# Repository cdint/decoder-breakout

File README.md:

# decoder-breakout
High-speed optical decoder breakout board with an I2C interface

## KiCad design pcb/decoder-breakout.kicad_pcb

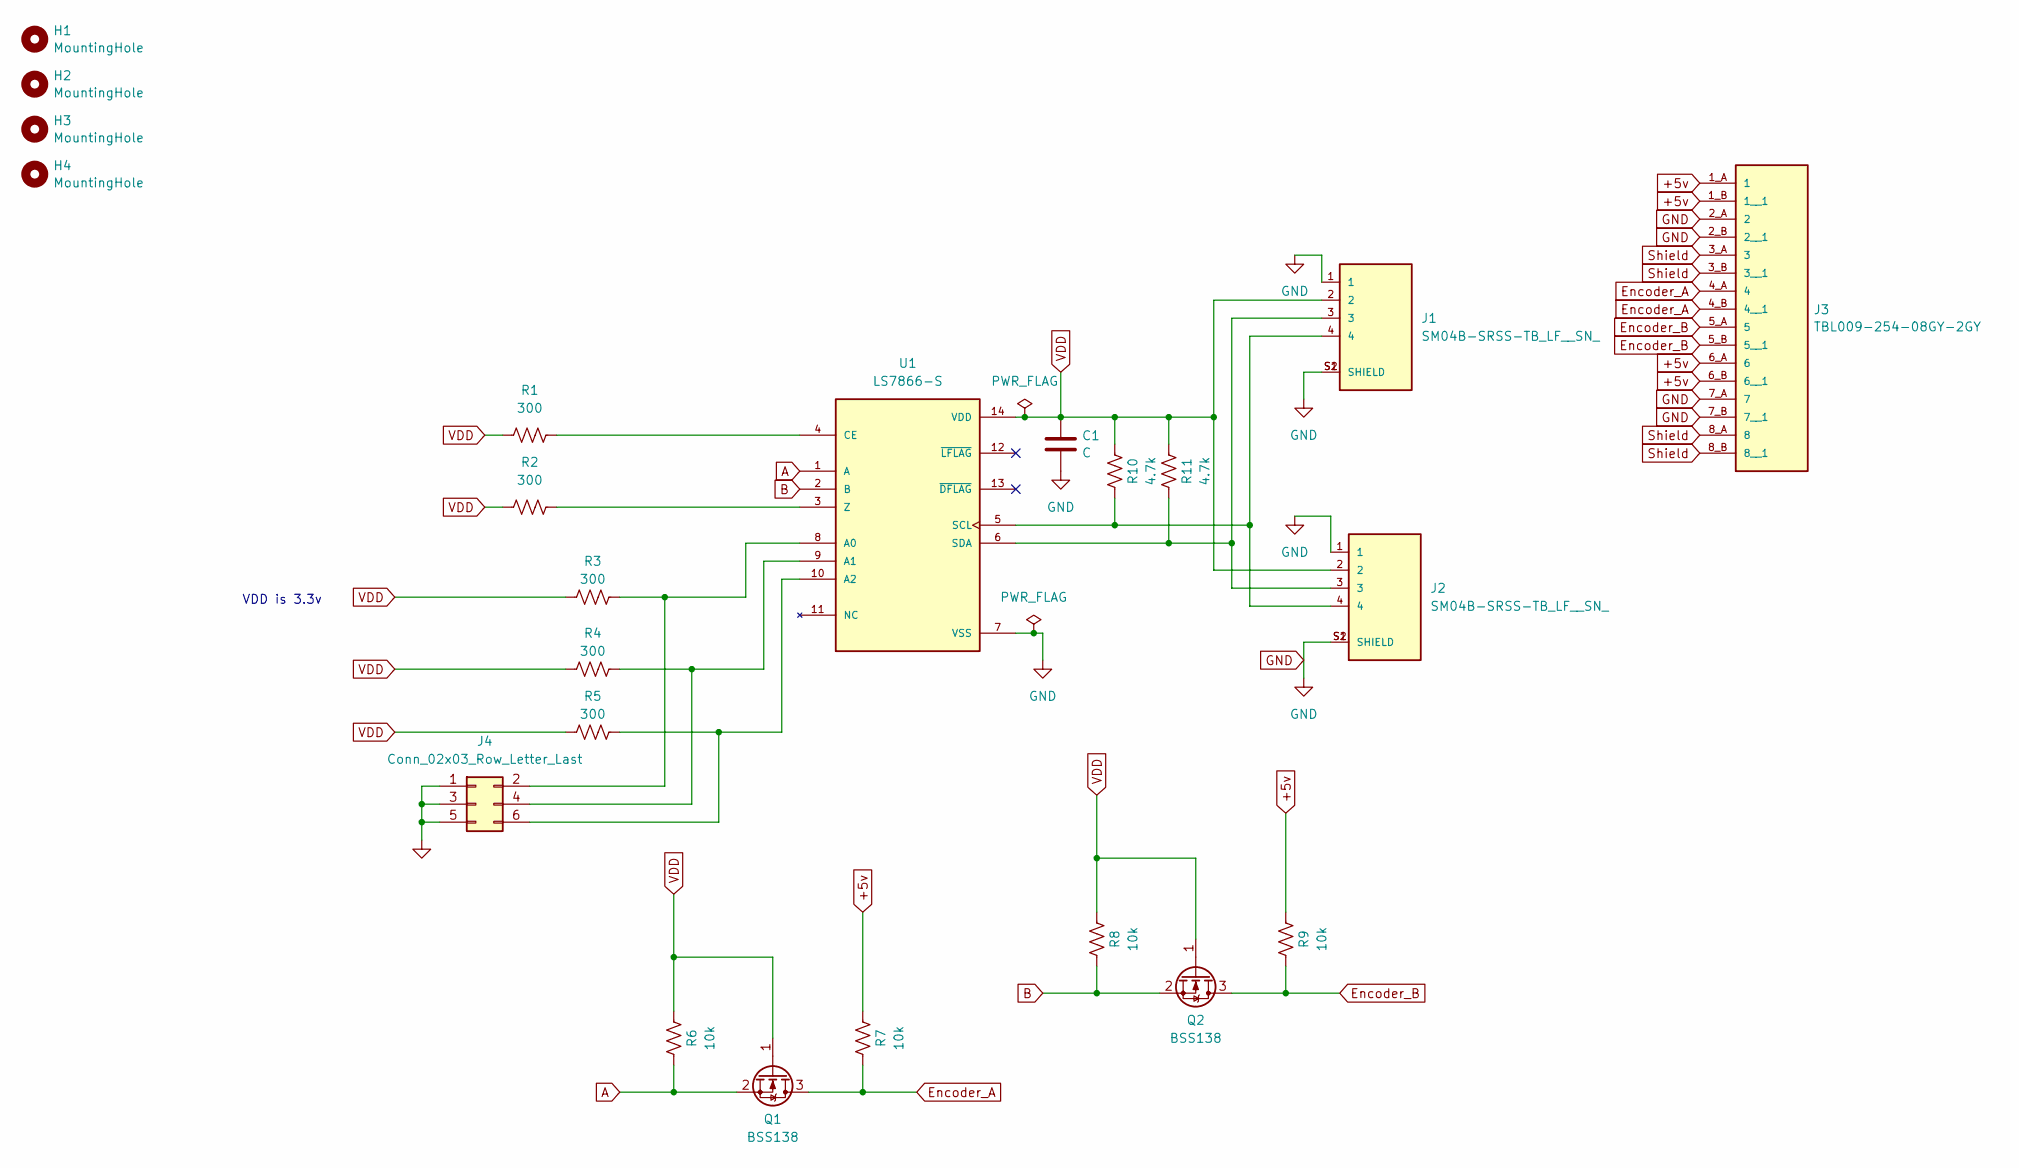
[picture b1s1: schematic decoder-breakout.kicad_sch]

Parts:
C1: C; C_1812_4532Metric_Pad1.57x3.40mm_HandSolder
H1, H2, H3, H4: MountingHole; MountingHole_2.5mm_Pad
J1, J2: SM04B-SRSS-TB_LF__SN_; JST_SM04B-SRSS-TB_LF__SN_
J3: TBL009-254-08GY-2GY; CUI_TBL009-254-08GY-2GY
J4: Conn_02x03_Row_Letter_Last; PinHeader_2x03_P2.54mm_Vertical
Q1, Q2: BSS138; SOT-23
R1, R2, R3, R4, R5: 300; R_2010_5025Metric_Pad1.40x2.65mm_HandSolder
R6, R7, R8, R9: 10k; R_2010_5025Metric_Pad1.40x2.65mm_HandSolder
R10, R11: 4.7k; R_2010_5025Metric_Pad1.40x2.65mm_HandSolder
U1: LS7866-S; SOIC127P600X175-14N; PARTREV June 2023

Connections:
+5v: J3.1_A (1), J3.1_B (1__1), J3.6_A (6), J3.6_B (6__1), R7.1, R9.1
A: Q1.2 (S), R6.2, U1.1 (A)
B: Q2.2 (S), R8.2, U1.2 (B)
Encoder_A: J3.4_A (4), J3.4_B (4__1), Q1.3 (D), R7.2
Encoder_B: J3.5_A (5), J3.5_B (5__1), Q2.3 (D), R9.2
GND: C1.2, J1.1, J1.S1 (SHIELD), J1.S2 (SHIELD), J2.1, J2.S1 (SHIELD), J2.S2 (SHIELD), J3.2_A (2), J3.2_B (2__1), J3.7_A (7), J3.7_B (7__1), J4.1, J4.3, J4.5, U1.7 (VSS)
unnamed: J4.2, R3.1, U1.8 (A0)
unnamed: J4.6, R5.1, U1.10 (A2)
unnamed: J4.4, R4.1, U1.9 (A1)
unnamed: R1.1, U1.4 (CE)
unnamed: J1.4, J2.4, R10.2, U1.5 (SCL)
unnamed: J1.3, J2.3, R11.2, U1.6 (SDA)
unnamed: R2.1, U1.3 (Z)
Shield: J3.3_A (3), J3.3_B (3__1), J3.8_A (8), J3.8_B (8__1)
VDD: C1.1, J1.2, J2.2, Q1.1 (G), Q2.1 (G), R1.2, R2.2, R3.2, R4.2, R5.2, R6.1, R8.1, R10.1, R11.1, U1.14 (VDD)

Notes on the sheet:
VDD is 3.3v

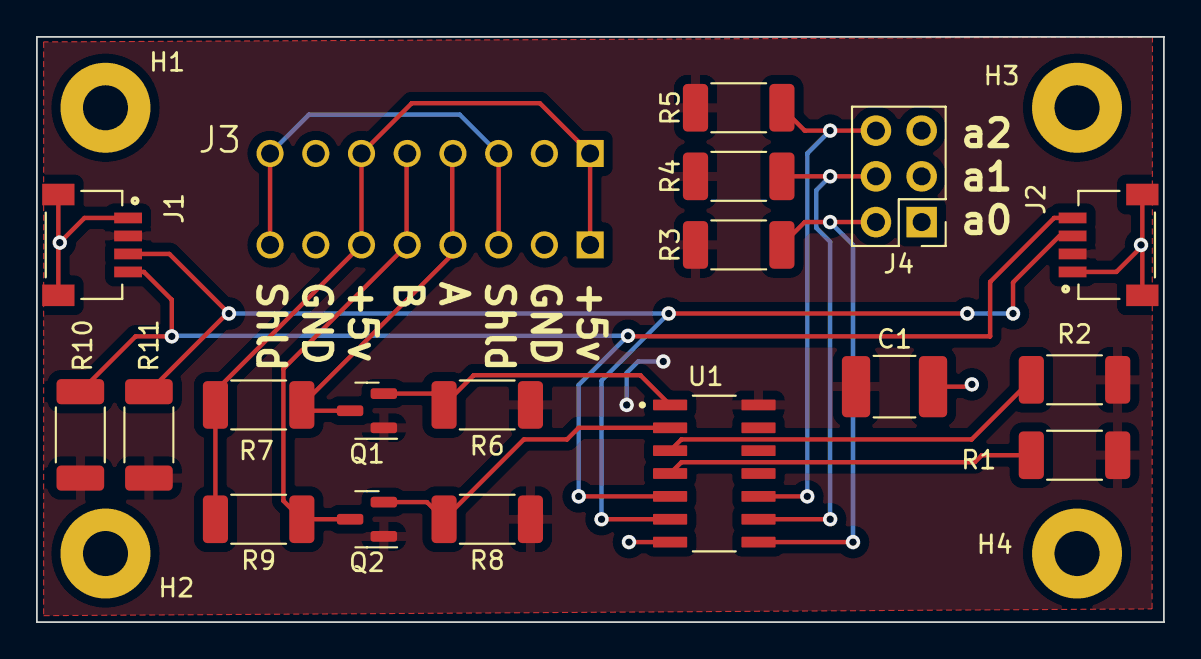
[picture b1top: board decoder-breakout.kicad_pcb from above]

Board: 2 copper layers, 62.6 x 32.5 mm, 23 parts (0 on the bottom side), 15 nets.

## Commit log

2024-04-16 initial commit, add LS7866 symbol and footprint
2024-05-09 add resistors and jumpers
2024-05-30 added jumpers for changing address, level shifters 3.3v->5v for encoders
2024-05-30 added terminal block, started on PCB
2024-07-02 pcb rough layout
2024-07-02 pcb adding filled zones and starting connections
2024-07-09 corrected jumper wiring
2024-07-09 clean up terminal block pins
    - add 10 and 14 pin terminal blocks for possible use in the future
2024-07-16 working on copper fill
2024-07-16 add decoupling cap, mounting holes and board edges
2024-08-06 Split terminal, add PCB screen print, consider shield-ground jumper
    Split terminal, add PCB screen print, consider shield-ground jumper
    summary of diff --git a/TODO.md b/TODO.md
    - Split terminal block into two: one for 5 pins for encoder, another for +5v, gnd, and shield
    - Add screen print to the PCB for identifying connections, possibly with a graphic for encoder connections
    - Consider adding a jumper to optionally connect shield and ground together
2024-08-06 WIP set up particle workbench and get compile working
2024-08-27 Replace HAL_I2C with Wire.write, update LS7866 headers
    Replace HAL_I2C_Mem_Write with Wire.write() in write_reg
    summary of diff --git a/src/photon2/src/LS7866.cpp b/src/photon2/src/LS7866.cpp
    - Add a comment to replace HAL_I2C_Mem_Write with Wire.write() in write_reg method
    Add stdint.h header, comment out i2c_hal in LS7866 class
    summary of diff --git a/src/photon2/src/LS7866.h b/src/photon2/src/LS7866.h
    - Include `<stdint.h>` header
2024-09-10 WIP LS7866 and photon 2 demo code
    - temporarily move src/* to .../junk/
    - experiment with demo code from https://lsicsi.com/products/ls7866/
2024-09-10 Disable counter 0, LED, SyncPin; enable counter 7; adjust I2C
    Disable counter 0, LED, SyncPin; enable counter 7; adjust I2C.
    summary of diff --git a/src/photon2/src/decoder-breakout.cpp b/src/photon2/src/decoder-breakout.cpp
    - Remove usage of counter 0 by commenting out its definition
    - Define counter 7 for use
    - Comment out LED and SyncPin related lines, effectively disabling LED operations and the usage of SyncPin
    - Disable `setLed` function calls by commenting them out in various parts of the code
2024-09-19 Update version, simplify chip setup, remove LED code
    Update PRM_VERSION, simplify chip setup, remove LED code
    summary of diff --git a/src/photon2/src/decoder-breakout.cpp b/src/photon2/src/decoder-breakout.cpp
    - Change PRM_VERSION from "1.00" to "0.1"
    - Comment out the definition of CNTR_7
    - Introduce definitions for ADDR_JUMPERS and CHIP_ADDR
    - Remove definitions for LED related constants and operations
2024-09-19 Add newline to Serial.print in ChipSetup and setup function
    Add newline to Serial.print and version message in setup
    summary of diff --git a/src/photon2/src/decoder-breakout.cpp b/src/photon2/src/decoder-breakout.cpp
    - Add newline character to Serial.print message in ChipSetup
    - Append newline character to version display message in setup function
2024-09-26 added I2C scanner
2024-10-03 Clarify LS7866 address bits; rename variable and update references.
    Clarify LS7866 high-order address bits fixed at 0x70
    summary of diff --git a/src/photon2/src/LS7866_Registers.h b/src/photon2/src/LS7866_Registers.h
    - Add comment to clarify that LS7866 high-order address bits are fixed at 0x70
    Rename variable and update its references in functions
    summary of diff --git a/src/photon2/src/decoder-breakout.cpp b/src/photon2/src/decoder-breakout.cpp
    - Rename `tsPollingInterval` variable to `nextPollMillis` in decoder-breakout.cpp
2024-10-03 Set firmware 5.8.0, p2; update I2C, fix includes, continuous scan.
    Add particle firmwareVersion 5.8.0 and targetPlatform p2
    summary of diff --git a/src/photon2addressScanner/.vscode/settings.json b/src/photon2addressScanner/.vscode/settings.json
    - Add "particle.firmwareVersion" with a value of "5.8.0"
    - Add "particle.targetPlatform" with a value of "p2"
    Update I2C scanner code for continuous scanning, fix includes
    summary of diff --git a/src/photon2addressScanner/src/L07_00_I2CScanner.cpp b/src/photon2addressScanner/src/L07_00_I2CScanner.cpp
2024-10-03 changed lowercase to Wire.h, set OS version
2024-10-17 Adjust PCB design, skip I2C reserved addresses, tweak delays
    Move, add junctions; adjust wires; update symbols, labels
    summary of diff --git a/pcb/decoder-breakout.kicad_sch b/pcb/decoder-breakout.kicad_sch
    - Move some junctions to new coordinates on the schematic
    - Add new junctions with unique UUIDs
    - Adjust wire connections to match new junction positions
    - Remove a junction and its associated wires
2024-10-24 Update CounterPoll format, disable Fast Mode, reduce delay
    Update CounterPoll format, disable Fast Mode, reduce delay
    summary of diff --git a/src/photon2/src/decoder-breakout.cpp b/src/photon2/src/decoder-breakout.cpp
    - Update formatting in CounterPoll function to include both decimal and hex representations of the counter value in the printed message
    - Disable setting I2C bus speed to Fast Mode 400K in setup function
    - Reduce the initial delay in setup function from 10000ms to 5000ms to accelerate startup
2024-11-07 Add BSS138_1 symbol, update datasheet position, change lib_id.
    Add BSS138_1 symbol; update datasheet position and lib_id
    summary of diff --git a/pcb/decoder-breakout.kicad_sch b/pcb/decoder-breakout.kicad_sch
    - Add symbol for BSS138_1 with properties including Reference, Value, Footprint, Datasheet, ki_keywords, ki_description, and ki_fp_filters
    - Define graphical representation with polylines and circles for BSS138_1 symbol, including stroke and fill specifications
    - Define pins for BSS138_1 symbol with names G, S, D and their respective positions and numbers
    - Update the Datasheet property position for existing elements to (5.08 -3.81 0)
2024-11-07 v0.1 as built
    Update components, adjust layers, change directory, add elements
    summary of diff --git a/pcb/decoder-breakout.kicad_pcb b/pcb/decoder-breakout.kicad_pcb
    - Update references and values for components Q2 and Q1
    - Adjust various line strokes and polygon fills on F.SilkS and F.CrtYd layers
    - Change model directory reference from KICAD6_3DMODEL_DIR to KICAD7_3DMODEL_DIR
    - Add new resistor footprints with specified attributes and dimensions
2024-11-07 generate BOM for v0.1
    Comment out patterns for .net, .dsn, .ses, .xml, .csv; add newline
    summary of diff --git a/.gitignore b/.gitignore
    - Comment out patterns for *.net in the .gitignore file
    - Comment out patterns for *.dsn and *.ses
    - Comment out patterns for *.xml and *.csv
    - Add a newline at the end of the file
2024-11-14 add nul to .gitignore
2024-11-14 write library split todo file
    Write a todo file describing what we need to do to split the LS7866
    code into a library and the application-specific code including loop()
    and setup() into a separate file. The goal is to make it easier for
    us and others to make use of the library code in other projects. Right
    now, setup() and loop() consist maily of test code that we are using
    during PCB development. We want to keep that test code separate from
2025-01-09 WIP replace jumper pins with a single 2x3 group
    - update schematic
    - still needs PCB update
2025-01-09 WIP replacing pin headers on PCB with 2x3 group
2025-01-16 v0.2 as built
    - add silkscreen to terminal block
    - group jumpers into 2x3 header
    - move board edge so terminal block hangs over
    - edit terminal block footprint locally to remove silkscreen box, so it does not error from being off board edge
2025-01-23 v0.3 as built
    - rotate J4 and add silkscreen
    - move R10 and R11 to allow more room around J3
2025-03-13 WIP split into app and library
    summary of diff --git a/src/photon2/src/decoder-breakout.cpp b/src/photon2/src/decoder-breakout.cpp
    - Update the file header to reflect the Decoder Breakout Board library for Particle Photon 2 and include PCB version information.
    - set `PRM_VERSION` to "0.3.1" with the board version.
    - Remove unused and commented-out code, including LED pin definitions and related functions.
    - Add comments `// XXX application` and `// XXX library` to mark application-specific and library code sections.
    - Add a comment questioning the purpose of resetting `DSTR` in the `CounterPoll` function.
2025-03-20 make LED blink green for up, red for down
2025-03-20 comment out the DSTR reset
2025-03-20 first draft of working library split
2025-03-20 first draft of working library split, fix version number to match board v0.1
2025-03-27 Clarify I2C code, warn of overruns, ensure data safety.
    Clarify I2C comments, check bytes, handle errors, ensure safety.
    summary of diff --git a/src/photon2/src/decoder-breakout.cpp b/src/photon2/src/decoder-breakout.cpp
    - Add comments around the Wire.requestFrom() function to clarify its purpose
    - Insert a detailed comment warning about potential buffer overrun and memory overwrite issues
    - Suggest checking the actual number of bytes read from the I2C device against the requested number
    - Propose returning an error code if the byte count does not match, ensuring data integrity
2025-03-27 Add, update, and format binaries, comments, and code for clarity.
    Add new binary file named p2_firmware_1743098744025.bin.
    summary of diff --git a/p2_firmware_1743098744025.bin b/p2_firmware_1743098744025.bin
    - Add the file `p2_firmware_1743098744025.bin` with mode 100644
    - Differ binary content between `/dev/null` and `b/p2_firmware_1743098744025.bin`
    Add binary file `p2_firmware_1743099914818.bin`, set mode to 100644.
    summary of diff --git a/p2_firmware_1743099914818.bin b/p2_firmware_1743099914818.bin
2025-03-27 Refactor code, update firmware, and improve class structure.
    Add binary file, set mode 100644, update index to 13d7fbc
    summary of diff --git a/p2_firmware_1743104476075.bin b/p2_firmware_1743104476075.bin
    - Add new binary file `p2_firmware_1743104476075.bin`
    - Set file mode to `100644`
    - Update index from `0000000` to `13d7fbc`
    Rename `msg2Buff`, reindent `setup`, setup LS7866, update calls
2025-03-30 Add binary files, adjust code for debugging, and enhance comments.
    Add new binary file, set mode to 100644
    summary of diff --git a/p2_firmware_1743216022158.bin b/p2_firmware_1743216022158.bin
    - Add new binary file p2_firmware_1743216022158.bin
    - Set file mode to 100644
    Add and set mode for new binary file: p2_firmware_1743227768695.bin
    summary of diff --git a/p2_firmware_1743227768695.bin b/p2_firmware_1743227768695.bin
2025-03-30 Add binary files, adjust buffer sizes, clean code comments
    Add binary file p2_firmware_1743298969420.bin, set mode 100644
    summary of diff --git a/p2_firmware_1743298969420.bin b/p2_firmware_1743298969420.bin
    - Add a new binary file named p2_firmware_1743298969420.bin
    - Set file mode to 100644
    Add p2_firmware_1743299865789.bin and set mode to 100644
    summary of diff --git a/p2_firmware_1743299865789.bin b/p2_firmware_1743299865789.bin
2025-04-03 Add Makefile and enhance blink code readability in photon2 directory
    Add Makefile to photon2 with build, flash, and monitor targets
    summary of diff --git a/src/photon2/Makefile b/src/photon2/Makefile
    - Add Makefile to the photon2 directory under src
    - Set the file mode to 100644
    - Include target 'all' that depends on 'ship' and 'monitor'
    - Define 'ship' target to depend on 'build' and 'flash'
